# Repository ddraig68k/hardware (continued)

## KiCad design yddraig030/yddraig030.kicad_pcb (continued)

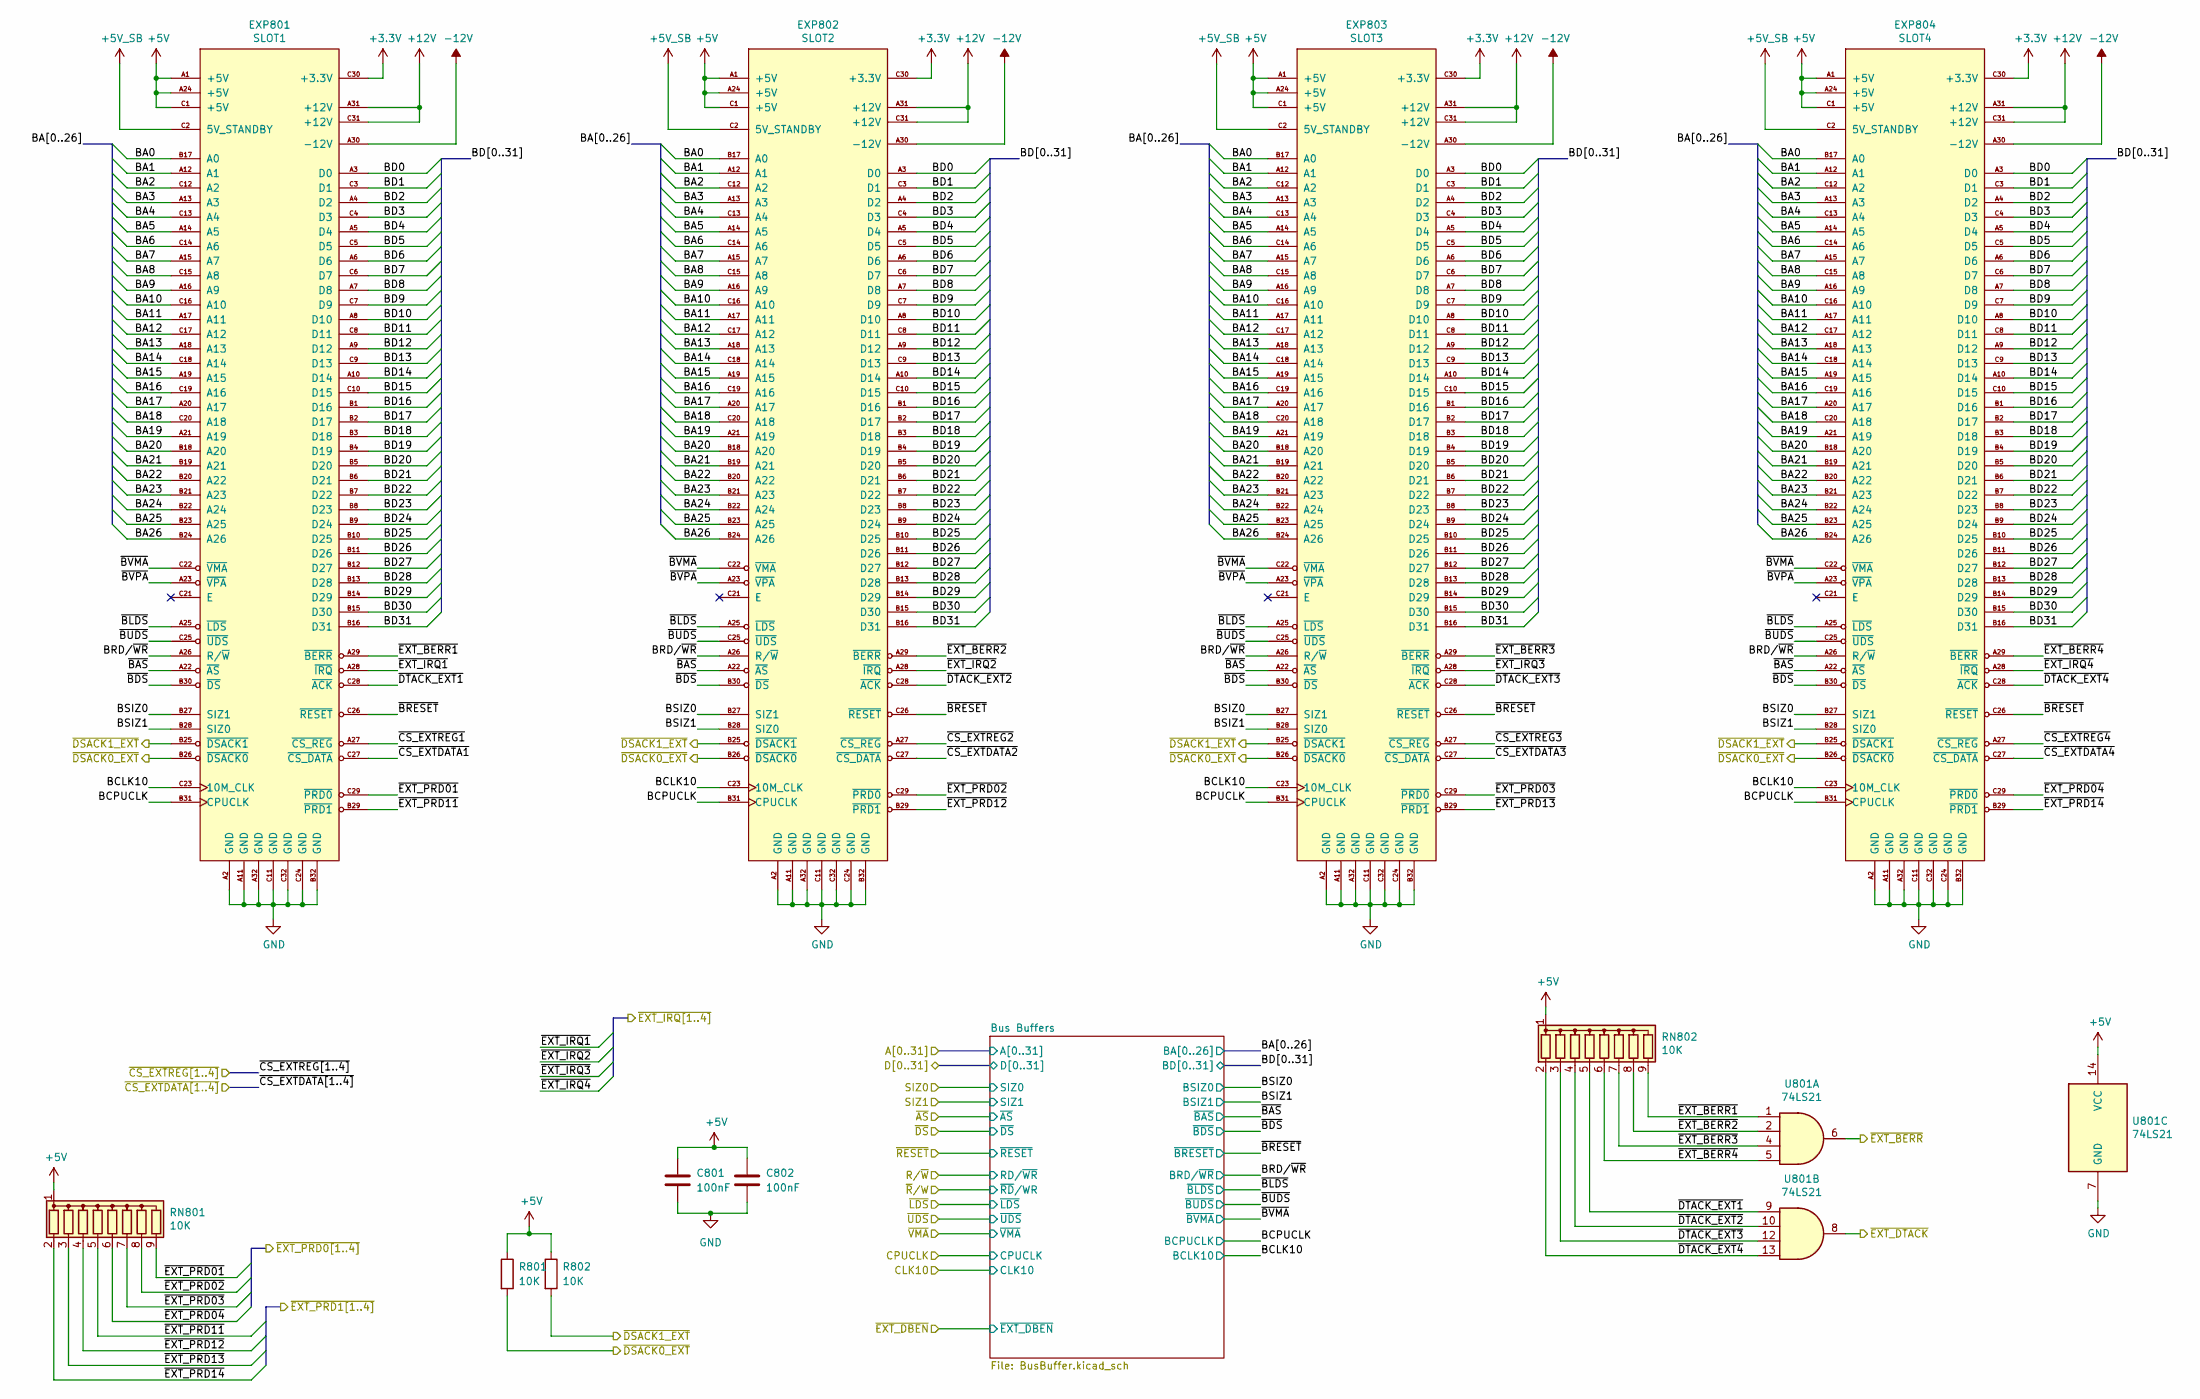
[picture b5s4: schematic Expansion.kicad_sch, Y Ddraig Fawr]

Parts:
C801, C802: 100nF; C_0805_2012Metric
EXP801: SLOT1; DIN41612_C_3x32_Female_Vertical_THT
EXP802: SLOT2; DIN41612_C_3x32_Female_Vertical_THT
EXP803: SLOT3; DIN41612_C_3x32_Female_Vertical_THT
EXP804: SLOT4; DIN41612_C_3x32_Female_Vertical_THT
R801, R802: 10K; R_0805_2012Metric
RN801, RN802: 10K; R_Array_SIP9
U801: 74LS21; SO-14_3.9x8.65mm_P1.27mm

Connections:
+3.3V: EXP801.C30 (+3.3V), EXP802.C30 (+3.3V), EXP803.C30 (+3.3V), EXP804.C30 (+3.3V); also elsewhere on the board
+5V: C801.1, C802.1, EXP801.A1 (+5V), EXP801.A24 (+5V), EXP801.C1 (+5V), EXP802.A1 (+5V), EXP802.A24 (+5V), EXP802.C1 (+5V), EXP803.A1 (+5V), EXP803.A24 (+5V), EXP803.C1 (+5V), EXP804.A1 (+5V), EXP804.A24 (+5V), EXP804.C1 (+5V), R801.1, R802.1, RN801.1 (common), RN802.1 (common), U801.14 (VCC); also elsewhere on the board
+5V_SB: EXP801.C2 (5V_STANDBY), EXP802.C2 (5V_STANDBY), EXP803.C2 (5V_STANDBY), EXP804.C2 (5V_STANDBY); also elsewhere on the board
+12V: EXP801.A31 (+12V), EXP801.C31 (+12V), EXP802.A31 (+12V), EXP802.C31 (+12V), EXP803.A31 (+12V), EXP803.C31 (+12V), EXP804.A31 (+12V), EXP804.C31 (+12V); also elsewhere on the board
-12V: EXP801.A30 (-12V), EXP802.A30 (-12V), EXP803.A30 (-12V), EXP804.A30 (-12V); also elsewhere on the board
/Decode and Logic/~DSACK0_EXT: EXP801.B26 (~DSACK0), EXP802.B26 (~DSACK0), EXP803.B26 (~DSACK0), EXP804.B26 (~DSACK0), R801.2; also elsewhere on the board
/Decode and Logic/~DSACK1_EXT: EXP801.B25 (~DSACK1), EXP802.B25 (~DSACK1), EXP803.B25 (~DSACK1), EXP804.B25 (~DSACK1), R802.2; also elsewhere on the board
/Decode and Logic/~EXT_BERR: U801.6; also elsewhere on the board
/Decode and Logic/~EXT_DTACK: U801.8; also elsewhere on the board
/Decode and Logic/~EXT_PRD01: EXP801.C29 (~PRD0), RN801.9 (R8); also elsewhere on the board
/Decode and Logic/~EXT_PRD02: EXP802.C29 (~PRD0), RN801.8 (R7); also elsewhere on the board
/Decode and Logic/~EXT_PRD03: EXP803.C29 (~PRD0), RN801.7 (R6); also elsewhere on the board
/Decode and Logic/~EXT_PRD04: EXP804.C29 (~PRD0), RN801.6 (R5); also elsewhere on the board
/Decode and Logic/~EXT_PRD11: EXP801.B29 (~PRD1), RN801.5 (R4); also elsewhere on the board
/Decode and Logic/~EXT_PRD12: EXP802.B29 (~PRD1), RN801.4 (R3); also elsewhere on the board
/Decode and Logic/~EXT_PRD13: EXP803.B29 (~PRD1), RN801.3 (R2); also elsewhere on the board
/Decode and Logic/~EXT_PRD14: EXP804.B29 (~PRD1), RN801.2 (R1); also elsewhere on the board
/Expansion Slots/BA0: EXP801.B17 (A0), EXP802.B17 (A0), EXP803.B17 (A0), EXP804.B17 (A0); also elsewhere on the board
/Expansion Slots/BA1: EXP801.A12 (A1), EXP802.A12 (A1), EXP803.A12 (A1), EXP804.A12 (A1); also elsewhere on the board
/Expansion Slots/BA2: EXP801.C12 (A2), EXP802.C12 (A2), EXP803.C12 (A2), EXP804.C12 (A2); also elsewhere on the board
/Expansion Slots/BA3: EXP801.A13 (A3), EXP802.A13 (A3), EXP803.A13 (A3), EXP804.A13 (A3); also elsewhere on the board
/Expansion Slots/BA4: EXP801.C13 (A4), EXP802.C13 (A4), EXP803.C13 (A4), EXP804.C13 (A4); also elsewhere on the board
/Expansion Slots/BA5: EXP801.A14 (A5), EXP802.A14 (A5), EXP803.A14 (A5), EXP804.A14 (A5); also elsewhere on the board
/Expansion Slots/BA6: EXP801.C14 (A6), EXP802.C14 (A6), EXP803.C14 (A6), EXP804.C14 (A6); also elsewhere on the board
/Expansion Slots/BA7: EXP801.A15 (A7), EXP802.A15 (A7), EXP803.A15 (A7), EXP804.A15 (A7); also elsewhere on the board
/Expansion Slots/BA8: EXP801.C15 (A8), EXP802.C15 (A8), EXP803.C15 (A8), EXP804.C15 (A8); also elsewhere on the board
/Expansion Slots/BA9: EXP801.A16 (A9), EXP802.A16 (A9), EXP803.A16 (A9), EXP804.A16 (A9); also elsewhere on the board
/Expansion Slots/BA10: EXP801.C16 (A10), EXP802.C16 (A10), EXP803.C16 (A10), EXP804.C16 (A10); also elsewhere on the board
/Expansion Slots/BA11: EXP801.A17 (A11), EXP802.A17 (A11), EXP803.A17 (A11), EXP804.A17 (A11); also elsewhere on the board
/Expansion Slots/BA12: EXP801.C17 (A12), EXP802.C17 (A12), EXP803.C17 (A12), EXP804.C17 (A12); also elsewhere on the board
/Expansion Slots/BA13: EXP801.A18 (A13), EXP802.A18 (A13), EXP803.A18 (A13), EXP804.A18 (A13); also elsewhere on the board
/Expansion Slots/BA14: EXP801.C18 (A14), EXP802.C18 (A14), EXP803.C18 (A14), EXP804.C18 (A14); also elsewhere on the board
/Expansion Slots/BA15: EXP801.A19 (A15), EXP802.A19 (A15), EXP803.A19 (A15), EXP804.A19 (A15); also elsewhere on the board
/Expansion Slots/BA16: EXP801.C19 (A16), EXP802.C19 (A16), EXP803.C19 (A16), EXP804.C19 (A16); also elsewhere on the board
/Expansion Slots/BA17: EXP801.A20 (A17), EXP802.A20 (A17), EXP803.A20 (A17), EXP804.A20 (A17); also elsewhere on the board
/Expansion Slots/BA18: EXP801.C20 (A18), EXP802.C20 (A18), EXP803.C20 (A18), EXP804.C20 (A18); also elsewhere on the board
/Expansion Slots/BA19: EXP801.A21 (A19), EXP802.A21 (A19), EXP803.A21 (A19), EXP804.A21 (A19); also elsewhere on the board
/Expansion Slots/BA20: EXP801.B18 (A20), EXP802.B18 (A20), EXP803.B18 (A20), EXP804.B18 (A20); also elsewhere on the board
/Expansion Slots/BA21: EXP801.B19 (A21), EXP802.B19 (A21), EXP803.B19 (A21), EXP804.B19 (A21); also elsewhere on the board
/Expansion Slots/BA22: EXP801.B20 (A22), EXP802.B20 (A22), EXP803.B20 (A22), EXP804.B20 (A22); also elsewhere on the board
/Expansion Slots/BA23: EXP801.B21 (A23), EXP802.B21 (A23), EXP803.B21 (A23), EXP804.B21 (A23); also elsewhere on the board
/Expansion Slots/BA24: EXP801.B22 (A24), EXP802.B22 (A24), EXP803.B22 (A24), EXP804.B22 (A24); also elsewhere on the board
/Expansion Slots/BA25: EXP801.B23 (A25), EXP802.B23 (A25), EXP803.B23 (A25), EXP804.B23 (A25); also elsewhere on the board
/Expansion Slots/BA26: EXP801.B24 (A26), EXP802.B24 (A26), EXP803.B24 (A26), EXP804.B24 (A26); also elsewhere on the board
/Expansion Slots/BCLK10: EXP801.C23 (10M_CLK), EXP802.C23 (10M_CLK), EXP803.C23 (10M_CLK), EXP804.C23 (10M_CLK); also elsewhere on the board
/Expansion Slots/BCPUCLK: EXP801.B31 (CPUCLK), EXP802.B31 (CPUCLK), EXP803.B31 (CPUCLK), EXP804.B31 (CPUCLK); also elsewhere on the board
/Expansion Slots/BD0: EXP801.A3 (D0), EXP802.A3 (D0), EXP803.A3 (D0), EXP804.A3 (D0); also elsewhere on the board
/Expansion Slots/BD1: EXP801.C3 (D1), EXP802.C3 (D1), EXP803.C3 (D1), EXP804.C3 (D1); also elsewhere on the board
/Expansion Slots/BD2: EXP801.A4 (D2), EXP802.A4 (D2), EXP803.A4 (D2), EXP804.A4 (D2); also elsewhere on the board
/Expansion Slots/BD3: EXP801.C4 (D3), EXP802.C4 (D3), EXP803.C4 (D3), EXP804.C4 (D3); also elsewhere on the board
/Expansion Slots/BD4: EXP801.A5 (D4), EXP802.A5 (D4), EXP803.A5 (D4), EXP804.A5 (D4); also elsewhere on the board
/Expansion Slots/BD5: EXP801.C5 (D5), EXP802.C5 (D5), EXP803.C5 (D5), EXP804.C5 (D5); also elsewhere on the board
/Expansion Slots/BD6: EXP801.A6 (D6), EXP802.A6 (D6), EXP803.A6 (D6), EXP804.A6 (D6); also elsewhere on the board
/Expansion Slots/BD7: EXP801.C6 (D7), EXP802.C6 (D7), EXP803.C6 (D7), EXP804.C6 (D7); also elsewhere on the board
/Expansion Slots/BD8: EXP801.A7 (D8), EXP802.A7 (D8), EXP803.A7 (D8), EXP804.A7 (D8); also elsewhere on the board
/Expansion Slots/BD9: EXP801.C7 (D9), EXP802.C7 (D9), EXP803.C7 (D9), EXP804.C7 (D9); also elsewhere on the board
/Expansion Slots/BD10: EXP801.A8 (D10), EXP802.A8 (D10), EXP803.A8 (D10), EXP804.A8 (D10); also elsewhere on the board
/Expansion Slots/BD11: EXP801.C8 (D11), EXP802.C8 (D11), EXP803.C8 (D11), EXP804.C8 (D11); also elsewhere on the board
/Expansion Slots/BD12: EXP801.A9 (D12), EXP802.A9 (D12), EXP803.A9 (D12), EXP804.A9 (D12); also elsewhere on the board
/Expansion Slots/BD13: EXP801.C9 (D13), EXP802.C9 (D13), EXP803.C9 (D13), EXP804.C9 (D13); also elsewhere on the board
/Expansion Slots/BD14: EXP801.A10 (D14), EXP802.A10 (D14), EXP803.A10 (D14), EXP804.A10 (D14); also elsewhere on the board
/Expansion Slots/BD15: EXP801.C10 (D15), EXP802.C10 (D15), EXP803.C10 (D15), EXP804.C10 (D15); also elsewhere on the board
/Expansion Slots/BD16: EXP801.B1 (D16), EXP802.B1 (D16), EXP803.B1 (D16), EXP804.B1 (D16); also elsewhere on the board
/Expansion Slots/BD17: EXP801.B2 (D17), EXP802.B2 (D17), EXP803.B2 (D17), EXP804.B2 (D17); also elsewhere on the board
/Expansion Slots/BD18: EXP801.B3 (D18), EXP802.B3 (D18), EXP803.B3 (D18), EXP804.B3 (D18); also elsewhere on the board
/Expansion Slots/BD19: EXP801.B4 (D19), EXP802.B4 (D19), EXP803.B4 (D19), EXP804.B4 (D19); also elsewhere on the board
/Expansion Slots/BD20: EXP801.B5 (D20), EXP802.B5 (D20), EXP803.B5 (D20), EXP804.B5 (D20); also elsewhere on the board
/Expansion Slots/BD21: EXP801.B6 (D21), EXP802.B6 (D21), EXP803.B6 (D21), EXP804.B6 (D21); also elsewhere on the board
/Expansion Slots/BD22: EXP801.B7 (D22), EXP802.B7 (D22), EXP803.B7 (D22), EXP804.B7 (D22); also elsewhere on the board
/Expansion Slots/BD23: EXP801.B8 (D23), EXP802.B8 (D23), EXP803.B8 (D23), EXP804.B8 (D23); also elsewhere on the board
/Expansion Slots/BD24: EXP801.B9 (D24), EXP802.B9 (D24), EXP803.B9 (D24), EXP804.B9 (D24); also elsewhere on the board
/Expansion Slots/BD25: EXP801.B10 (D25), EXP802.B10 (D25), EXP803.B10 (D25), EXP804.B10 (D25); also elsewhere on the board
/Expansion Slots/BD26: EXP801.B11 (D26), EXP802.B11 (D26), EXP803.B11 (D26), EXP804.B11 (D26); also elsewhere on the board
/Expansion Slots/BD27: EXP801.B12 (D27), EXP802.B12 (D27), EXP803.B12 (D27), EXP804.B12 (D27); also elsewhere on the board
/Expansion Slots/BD28: EXP801.B13 (D28), EXP802.B13 (D28), EXP803.B13 (D28), EXP804.B13 (D28); also elsewhere on the board
/Expansion Slots/BD29: EXP801.B14 (D29), EXP802.B14 (D29), EXP803.B14 (D29), EXP804.B14 (D29); also elsewhere on the board
/Expansion Slots/BD30: EXP801.B15 (D30), EXP802.B15 (D30), EXP803.B15 (D30), EXP804.B15 (D30); also elsewhere on the board
/Expansion Slots/BD31: EXP801.B16 (D31), EXP802.B16 (D31), EXP803.B16 (D31), EXP804.B16 (D31); also elsewhere on the board
/Expansion Slots/BRD/~WR: EXP801.A26 (R/~W), EXP802.A26 (R/~W), EXP803.A26 (R/~W), EXP804.A26 (R/~W); also elsewhere on the board
/Expansion Slots/BSIZ0: EXP801.B27 (SIZ1), EXP802.B27 (SIZ1), EXP803.B27 (SIZ1), EXP804.B27 (SIZ1); also elsewhere on the board
/Expansion Slots/BSIZ1: EXP801.B28 (SIZ0), EXP802.B28 (SIZ0), EXP803.B28 (SIZ0), EXP804.B28 (SIZ0); also elsewhere on the board
/Expansion Slots/~BAS: EXP801.A22 (~AS), EXP802.A22 (~AS), EXP803.A22 (~AS), EXP804.A22 (~AS); also elsewhere on the board
/Expansion Slots/~BDS: EXP801.B30 (~DS), EXP802.B30 (~DS), EXP803.B30 (~DS), EXP804.B30 (~DS); also elsewhere on the board
/Expansion Slots/~BLDS: EXP801.A25 (~LDS), EXP802.A25 (~LDS), EXP803.A25 (~LDS), EXP804.A25 (~LDS); also elsewhere on the board
/Expansion Slots/~BRESET: EXP801.C26 (~RESET), EXP802.C26 (~RESET), EXP803.C26 (~RESET), EXP804.C26 (~RESET); also elsewhere on the board
/Expansion Slots/~BUDS: EXP801.C25 (~UDS), EXP802.C25 (~UDS), EXP803.C25 (~UDS), EXP804.C25 (~UDS); also elsewhere on the board
/Expansion Slots/~BVMA: EXP801.C22 (~VMA), EXP802.C22 (~VMA), EXP803.C22 (~VMA), EXP804.C22 (~VMA); also elsewhere on the board
/Expansion Slots/~BVPA: EXP801.A23 (~VPA), EXP802.A23 (~VPA), EXP803.A23 (~VPA), EXP804.A23 (~VPA)
/Expansion Slots/~CS_EXTDATA1: EXP801.C27 (~CS_DATA); also elsewhere on the board
/Expansion Slots/~CS_EXTDATA2: EXP802.C27 (~CS_DATA); also elsewhere on the board
/Expansion Slots/~CS_EXTDATA3: EXP803.C27 (~CS_DATA); also elsewhere on the board
/Expansion Slots/~CS_EXTDATA4: EXP804.C27 (~CS_DATA); also elsewhere on the board
/Expansion Slots/~CS_EXTREG1: EXP801.A27 (~CS_REG); also elsewhere on the board
/Expansion Slots/~CS_EXTREG2: EXP802.A27 (~CS_REG); also elsewhere on the board
/Expansion Slots/~CS_EXTREG3: EXP803.A27 (~CS_REG); also elsewhere on the board
/Expansion Slots/~CS_EXTREG4: EXP804.A27 (~CS_REG); also elsewhere on the board
/Expansion Slots/~DTACK_EXT1: EXP801.C28 (~ACK), RN802.5 (R4), U801.9
/Expansion Slots/~DTACK_EXT2: EXP802.C28 (~ACK), RN802.4 (R3), U801.10
/Expansion Slots/~DTACK_EXT3: EXP803.C28 (~ACK), RN802.3 (R2), U801.12
/Expansion Slots/~DTACK_EXT4: EXP804.C28 (~ACK), RN802.2 (R1), U801.13
/Expansion Slots/~EXT_BERR1: EXP801.A29 (~BERR), RN802.9 (R8), U801.1
/Expansion Slots/~EXT_BERR2: EXP802.A29 (~BERR), RN802.8 (R7), U801.2
/Expansion Slots/~EXT_BERR3: EXP803.A29 (~BERR), RN802.7 (R6), U801.4
/Expansion Slots/~EXT_BERR4: EXP804.A29 (~BERR), RN802.6 (R5), U801.5
/Expansion Slots/~EXT_IRQ1: EXP801.A28 (~IRQ); also elsewhere on the board
/Expansion Slots/~EXT_IRQ2: EXP802.A28 (~IRQ); also elsewhere on the board
/Expansion Slots/~EXT_IRQ3: EXP803.A28 (~IRQ); also elsewhere on the board
/Expansion Slots/~EXT_IRQ4: EXP804.A28 (~IRQ); also elsewhere on the board

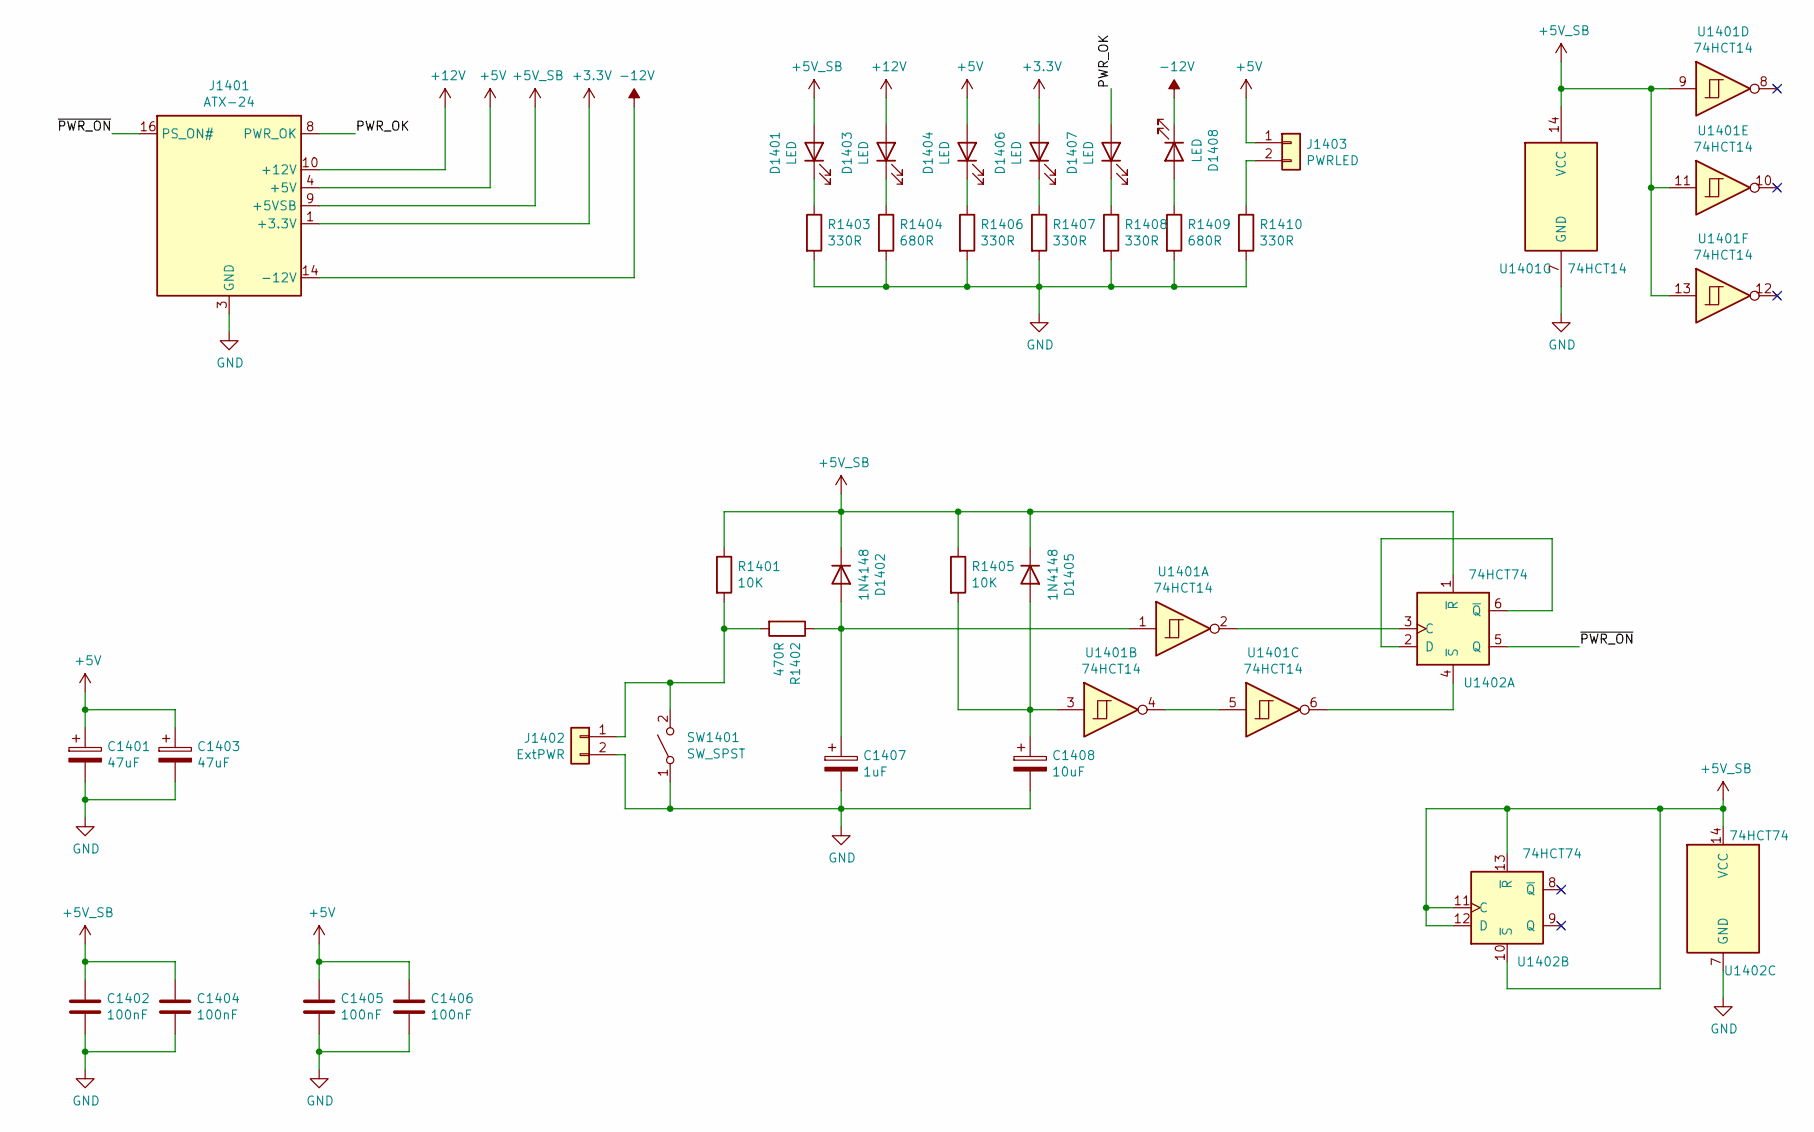
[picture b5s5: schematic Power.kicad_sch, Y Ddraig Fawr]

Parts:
C1401, C1403: 47uF; CP_Elec_4x5.3
C1402, C1404, C1405, C1406: 100nF; C_0805_2012Metric
C1407: 1uF; CP_Elec_4x5.3
C1408: 10uF; CP_Elec_4x5.3
D1401, D1403, D1404, D1406, D1407, D1408: LED; LED_1206_3216Metric
D1402, D1405: 1N4148; D_SOD-123
J1401: ATX-24; 1-1775099-3
J1402: ExtPWR; PinHeader_1x02_P2.54mm_Vertical
J1403: PWRLED; PinHeader_1x02_P2.54mm_Vertical
R1401, R1405: 10K; R_0805_2012Metric
R1402: 470R; R_0805_2012Metric
R1403, R1406, R1407, R1408, R1410: 330R; R_0805_2012Metric
R1404, R1409: 680R; R_0805_2012Metric
SW1401: SW_SPST; SW_PUSH_6mm_H4.3mm
U1401: 74HCT14; SO-14_3.9x8.65mm_P1.27mm
U1402: 74HCT74; SO-14_3.9x8.65mm_P1.27mm

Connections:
+3.3V: D1406.2 (A), J1401.1 (+3.3V), J1401.2 (+3.3V), J1401.12 (+3.3V), J1401.13 (+3.3V); also elsewhere on the board
+5V: C1401.1, C1403.1, C1405.1, C1406.1, D1404.2 (A), J1401.4 (+5V), J1401.6 (+5V), J1401.21 (+5V), J1401.22 (+5V), J1401.23 (+5V), J1403.1; also elsewhere on the board
+5V_SB: C1402.1, C1404.1, D1401.2 (A), D1402.1 (K), D1405.1 (K), J1401.9 (+5VSB), R1401.1, R1405.1, U1401.9, U1401.11, U1401.13, U1401.14 (VCC), U1402.1 (~R), U1402.10 (~S), U1402.11 (C), U1402.12 (D), U1402.13 (~R), U1402.14 (VCC); also elsewhere on the board
+12V: D1403.2 (A), J1401.10 (+12V), J1401.11 (+12V); also elsewhere on the board
-12V: D1408.1 (K), J1401.14 (-12V); also elsewhere on the board
/Power/PWR_OK: D1407.2 (A), J1401.8 (PWR_OK)
/Power/~PWR_ON: J1401.16 (PS_ON#), U1402.5 (Q)
unnamed: C1407.1, D1402.2 (A), R1402.1, U1401.1
unnamed: C1408.1, D1405.2 (A), R1405.2, U1401.3
unnamed: D1401.1 (K), R1403.1
unnamed: D1403.1 (K), R1404.1
unnamed: D1404.1 (K), R1406.1
unnamed: D1406.1 (K), R1407.1
unnamed: D1407.1 (K), R1408.1
unnamed: D1408.2 (A), R1409.1
unnamed: J1402.1, R1401.2, R1402.2, SW1401.2 (B)
unnamed: J1403.2, R1410.1
unnamed: U1401.2, U1402.3 (C)
unnamed: U1401.4, U1401.5
unnamed: U1401.6, U1402.4 (~S)
unnamed: U1402.2 (D), U1402.6 (~Q)

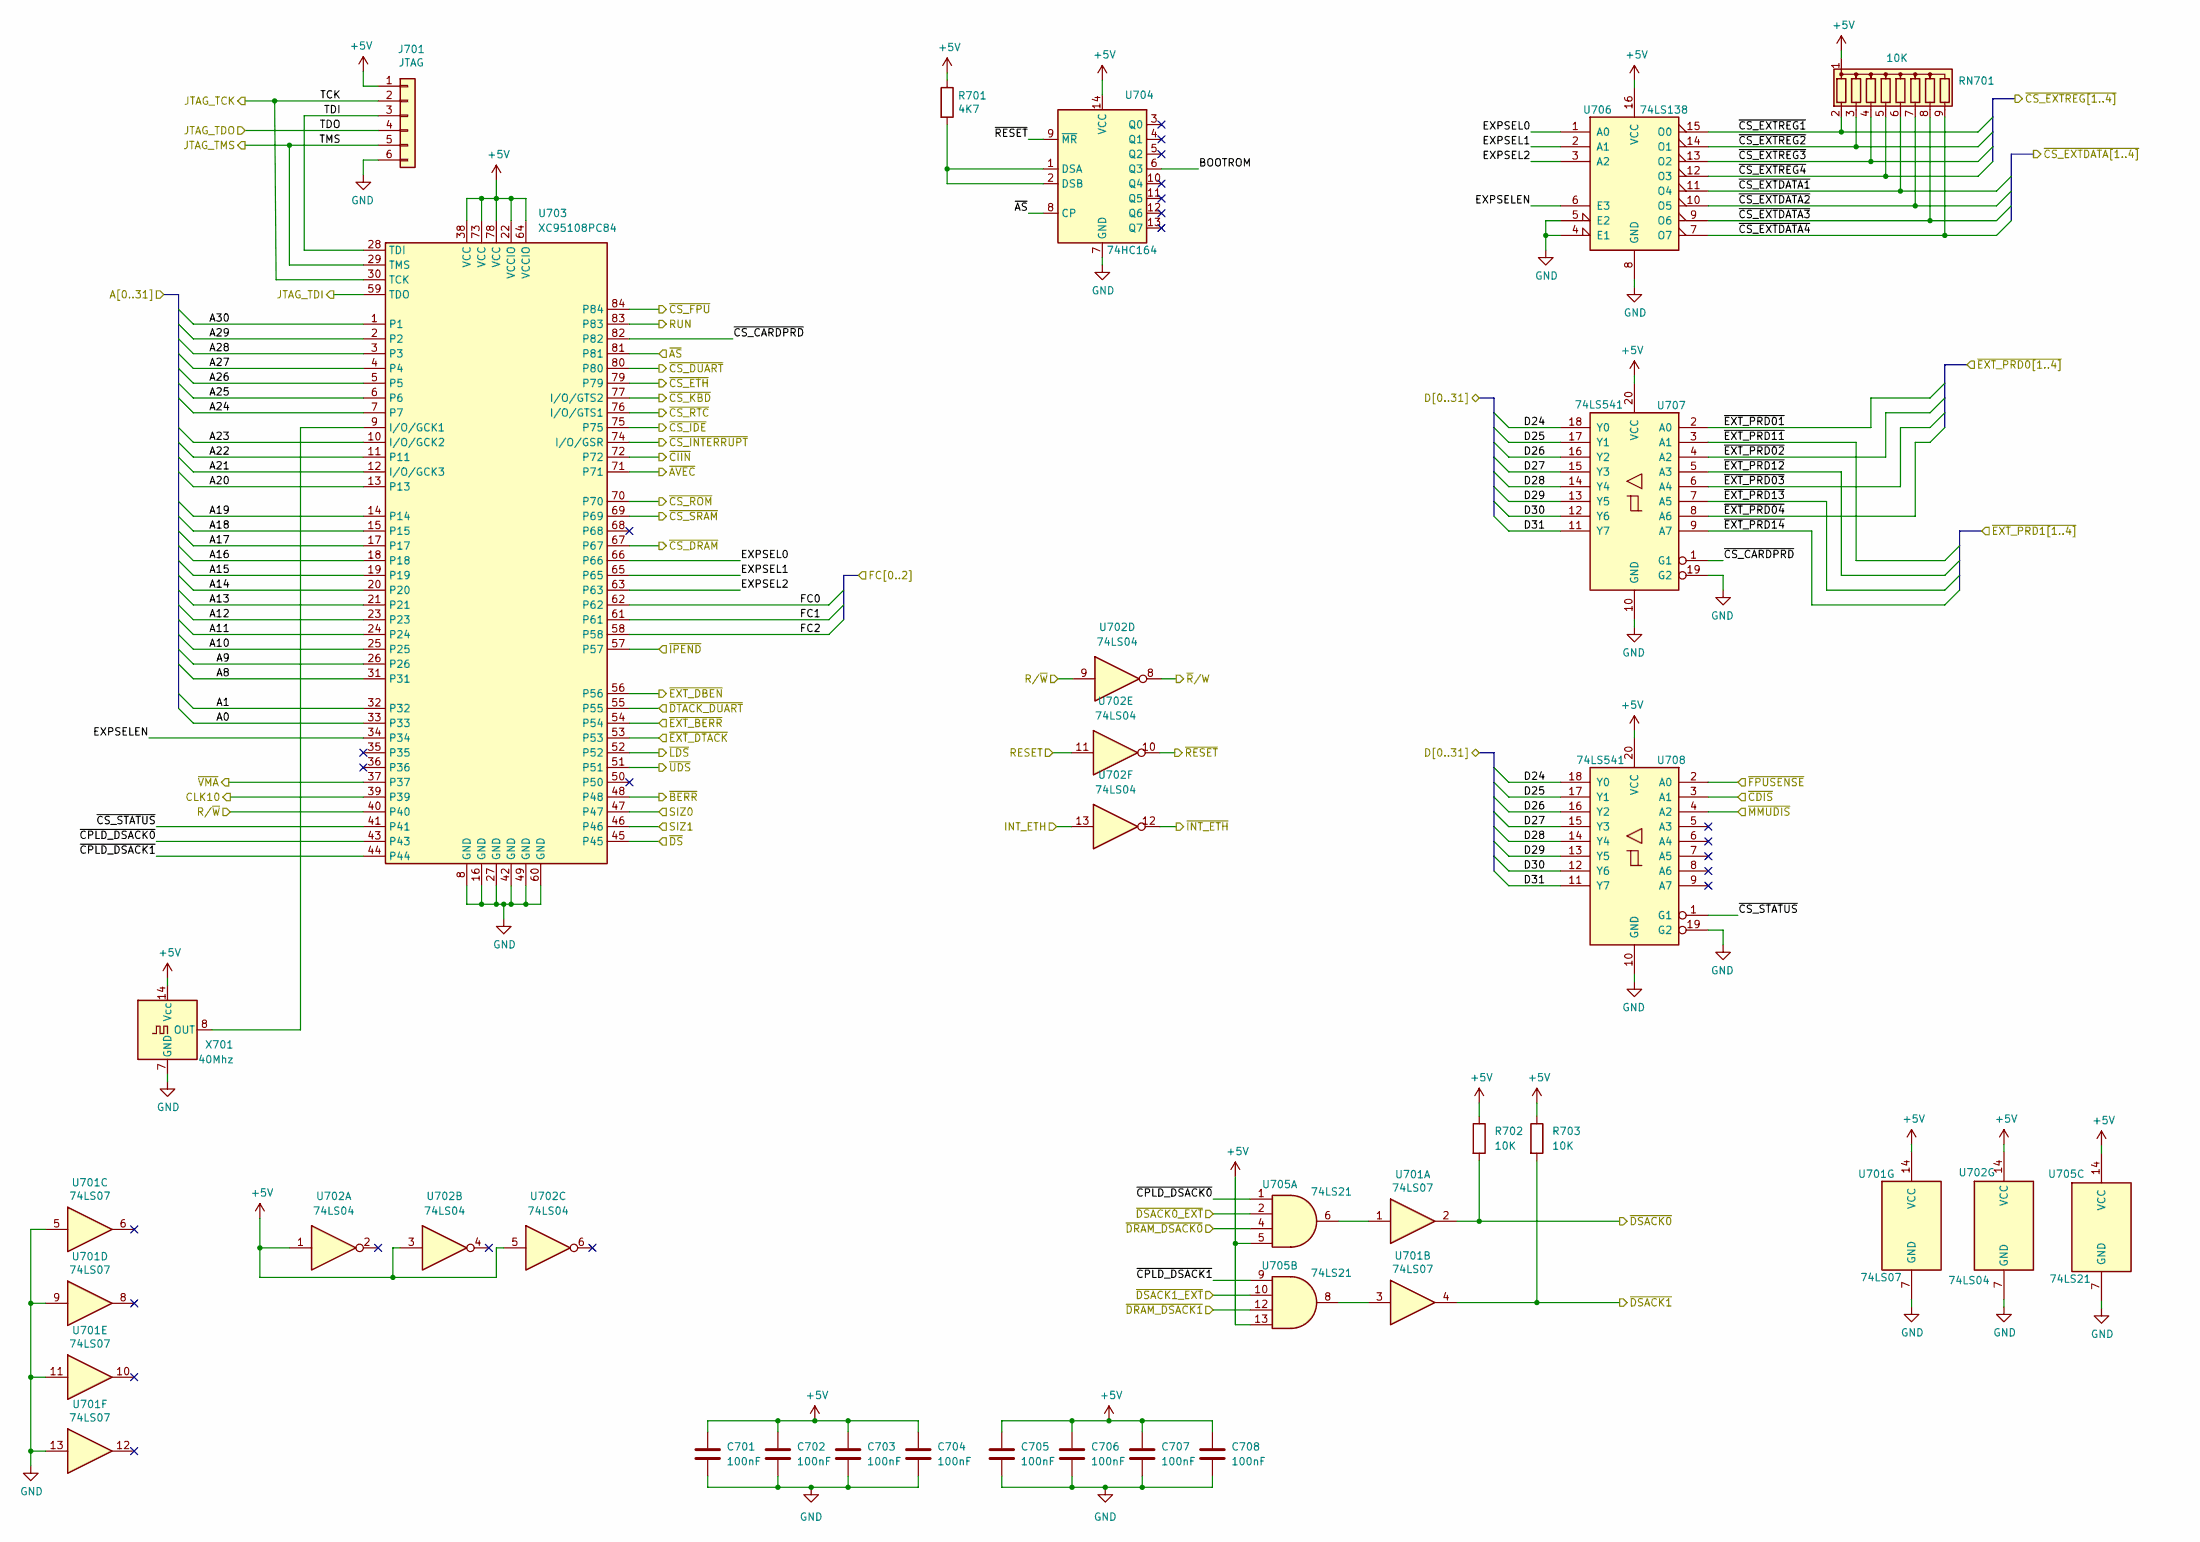
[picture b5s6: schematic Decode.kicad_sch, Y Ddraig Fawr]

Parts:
C701, C702, C703, C704, C705, C706, C707, C708: 100nF; C_0805_2012Metric
J701: JTAG; PinSocket_1x06_P2.54mm_Vertical
R701: 4K7; R_0805_2012Metric
R702, R703: 10K; R_0805_2012Metric
RN701: 10K; R_Array_SIP9
U701: 74LS07; SO-14_3.9x8.65mm_P1.27mm
U702: 74LS04; SO-14_3.9x8.65mm_P1.27mm
U703: XC95108PC84; PLCC-84_THT-Socket
U704: 74HC164; SO-14_3.9x8.65mm_P1.27mm
U705: 74LS21; SO-14_3.9x8.65mm_P1.27mm
U706: 74LS138; SO-16_3.9x9.9mm_P1.27mm
U707, U708: 74LS541; SO-20_5.3x12.6mm_P1.27mm
X701: 40Mhz; Oscillator_DIP-14

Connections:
+5V: C701.1, C702.1, C703.1, C704.1, C705.1, C706.1, C707.1, C708.1, J701.1, R701.1, R702.1, R703.1, RN701.1 (common), U701.14 (VCC), U702.1, U702.3, U702.5, U702.14 (VCC), U703.22 (VCCIO), U703.38 (VCC), U703.64 (VCCIO), U703.73 (VCC), U703.78 (VCC), U704.14 (VCC), U705.5, U705.13, U705.14 (VCC), U706.16 (VCC), U707.20 (VCC), U708.20 (VCC), X701.14 (Vcc); also elsewhere on the board
/CPU and FPU/FC0: U703.62; also elsewhere on the board
/CPU and FPU/FC1: U703.61; also elsewhere on the board
/CPU and FPU/FC2: U703.58; also elsewhere on the board
/CPU and FPU/R/~W: U702.9, U703.40; also elsewhere on the board
/CPU and FPU/~AS: U703.81, U704.8 (CP); also elsewhere on the board
/CPU and FPU/~AVEC: U703.71; also elsewhere on the board
/CPU and FPU/~BERR: U703.48; also elsewhere on the board
/CPU and FPU/~CDIS: U708.3 (A1); also elsewhere on the board
/CPU and FPU/~CIIN: U703.72; also elsewhere on the board
/CPU and FPU/~CS_FPU: U703.84; also elsewhere on the board
/CPU and FPU/~DSACK0: R702.2, U701.2; also elsewhere on the board
/CPU and FPU/~DSACK1: R703.2, U701.4; also elsewhere on the board
/CPU and FPU/~DS: U703.45; also elsewhere on the board
/CPU and FPU/~FPUSENSE: U708.2 (A0); also elsewhere on the board
/CPU and FPU/~IPEND: U703.57; also elsewhere on the board
/CPU and FPU/~MMUDIS: U708.4 (A2); also elsewhere on the board
/CPU and FPU/~RESET: U702.10, U704.9 (~MR); also elsewhere on the board
/DRAM/JTAG_TDI: U703.59 (TDO); also elsewhere on the board
/DRAM/~CS_DRAM: U703.67; also elsewhere on the board
/DRAM/~DSACK0: U705.4; also elsewhere on the board
/DRAM/~DSACK1: U705.12; also elsewhere on the board
/Decode and Logic/BOOTROM: U704.6 (Q3)
/Decode and Logic/CLK10: U703.39; also elsewhere on the board
/Decode and Logic/EXPSEL0: U703.66, U706.1 (A0)
/Decode and Logic/EXPSEL1: U703.65, U706.2 (A1)
/Decode and Logic/EXPSEL2: U703.63, U706.3 (A2)
/Decode and Logic/EXPSELEN: U703.34, U706.6 (E3)
/Decode and Logic/INT_ETH: U702.13; also elsewhere on the board
/Decode and Logic/RESET: U702.11; also elsewhere on the board
/Decode and Logic/RUN: U703.83; also elsewhere on the board
/Decode and Logic/SIZ0: U703.47
/Decode and Logic/SIZ1: U703.46
/Decode and Logic/TCK: J701.2, U703.30 (TCK); also elsewhere on the board
/Decode and Logic/TDI: J701.3, U703.28 (TDI)
/Decode and Logic/TDO: J701.4; also elsewhere on the board
/Decode and Logic/TMS: J701.5, U703.29 (TMS); also elsewhere on the board
/Decode and Logic/~CPLD_DSACK0: U703.43, U705.1
/Decode and Logic/~CPLD_DSACK1: U703.44, U705.9
/Decode and Logic/~CS_CARDPRD: U703.82, U707.1 (G1)
/Decode and Logic/~CS_DUART: U703.80; also elsewhere on the board
/Decode and Logic/~CS_ETH: U703.79; also elsewhere on the board
/Decode and Logic/~CS_IDE: U703.75; also elsewhere on the board
/Decode and Logic/~CS_INTERRUPT: U703.74 (I/O/GSR); also elsewhere on the board
/Decode and Logic/~CS_KBD: U703.77 (I/O/GTS2); also elsewhere on the board
/Decode and Logic/~CS_ROM: U703.70; also elsewhere on the board
/Decode and Logic/~CS_RTC: U703.76 (I/O/GTS1); also elsewhere on the board
/Decode and Logic/~CS_SRAM: U703.69; also elsewhere on the board
/Decode and Logic/~CS_STATUS: U703.41, U708.1 (G1)
/Decode and Logic/~DSACK0_EXT: U705.2; also elsewhere on the board
/Decode and Logic/~DSACK1_EXT: U705.10; also elsewhere on the board
/Decode and Logic/~DTACK_DUART: U703.55; also elsewhere on the board
/Decode and Logic/~EXT_BERR: U703.54; also elsewhere on the board
/Decode and Logic/~EXT_DBEN: U703.56; also elsewhere on the board
/Decode and Logic/~EXT_DTACK: U703.53; also elsewhere on the board
/Decode and Logic/~EXT_PRD01: U707.2 (A0); also elsewhere on the board
/Decode and Logic/~EXT_PRD02: U707.4 (A2); also elsewhere on the board
/Decode and Logic/~EXT_PRD03: U707.6 (A4); also elsewhere on the board
/Decode and Logic/~EXT_PRD04: U707.8 (A6); also elsewhere on the board
/Decode and Logic/~EXT_PRD11: U707.3 (A1); also elsewhere on the board
/Decode and Logic/~EXT_PRD12: U707.5 (A3); also elsewhere on the board
/Decode and Logic/~EXT_PRD13: U707.7 (A5); also elsewhere on the board
/Decode and Logic/~EXT_PRD14: U707.9 (A7); also elsewhere on the board
/Decode and Logic/~INT_ETH: U702.12; also elsewhere on the board
/Decode and Logic/~LDS: U703.52; also elsewhere on the board
/Decode and Logic/~R/W: U702.8; also elsewhere on the board
/Decode and Logic/~UDS: U703.51; also elsewhere on the board
/Decode and Logic/~VMA: U703.37; also elsewhere on the board
/Expansion Slots/~CS_EXTDATA1: RN701.6 (R5), U706.11 (O4); also elsewhere on the board
/Expansion Slots/~CS_EXTDATA2: RN701.7 (R6), U706.10 (O5); also elsewhere on the board
/Expansion Slots/~CS_EXTDATA3: RN701.8 (R7), U706.9 (O6); also elsewhere on the board
/Expansion Slots/~CS_EXTDATA4: RN701.9 (R8), U706.7 (O7); also elsewhere on the board
/Expansion Slots/~CS_EXTREG1: RN701.2 (R1), U706.15 (O0); also elsewhere on the board
/Expansion Slots/~CS_EXTREG2: RN701.3 (R2), U706.14 (O1); also elsewhere on the board
/Expansion Slots/~CS_EXTREG3: RN701.4 (R3), U706.13 (O2); also elsewhere on the board
/Expansion Slots/~CS_EXTREG4: RN701.5 (R4), U706.12 (O3); also elsewhere on the board
/ROM and SRAM/A0: U703.33; also elsewhere on the board
/ROM and SRAM/A1: U703.32; also elsewhere on the board
/ROM and SRAM/A8: U703.31; also elsewhere on the board
/ROM and SRAM/A9: U703.26; also elsewhere on the board
/ROM and SRAM/A10: U703.25; also elsewhere on the board
/ROM and SRAM/A11: U703.24; also elsewhere on the board
/ROM and SRAM/A12: U703.23; also elsewhere on the board
/ROM and SRAM/A13: U703.21; also elsewhere on the board
/ROM and SRAM/A14: U703.20; also elsewhere on the board
/ROM and SRAM/A15: U703.19; also elsewhere on the board
/ROM and SRAM/A16: U703.18; also elsewhere on the board
/ROM and SRAM/A17: U703.17; also elsewhere on the board
/ROM and SRAM/A18: U703.15; also elsewhere on the board
/ROM and SRAM/A19: U703.14; also elsewhere on the board
/ROM and SRAM/A20: U703.13; also elsewhere on the board
/ROM and SRAM/A21: U703.12 (I/O/GCK3); also elsewhere on the board
/ROM and SRAM/A22: U703.11; also elsewhere on the board
/ROM and SRAM/A23: U703.10 (I/O/GCK2); also elsewhere on the board
/ROM and SRAM/A24: U703.7; also elsewhere on the board
/ROM and SRAM/A25: U703.6; also elsewhere on the board
/ROM and SRAM/A26: U703.5; also elsewhere on the board
/ROM and SRAM/A27: U703.4; also elsewhere on the board
/ROM and SRAM/A28: U703.3; also elsewhere on the board
/ROM and SRAM/A29: U703.2; also elsewhere on the board
/ROM and SRAM/A30: U703.1; also elsewhere on the board
/ROM and SRAM/D24: U707.18 (Y0), U708.18 (Y0); also elsewhere on the board
/ROM and SRAM/D25: U707.17 (Y1), U708.17 (Y1); also elsewhere on the board
/ROM and SRAM/D26: U707.16 (Y2), U708.16 (Y2); also elsewhere on the board
/ROM and SRAM/D27: U707.15 (Y3), U708.15 (Y3); also elsewhere on the board
/ROM and SRAM/D28: U707.14 (Y4), U708.14 (Y4); also elsewhere on the board
/ROM and SRAM/D29: U707.13 (Y5), U708.13 (Y5); also elsewhere on the board
/ROM and SRAM/D30: U707.12 (Y6), U708.12 (Y6); also elsewhere on the board
/ROM and SRAM/D31: U707.11 (Y7), U708.11 (Y7); also elsewhere on the board
unnamed: R701.2, U704.1 (DSA), U704.2 (DSB)
unnamed: U701.1, U705.6
unnamed: U701.3, U705.8
unnamed: U703.9 (I/O/GCK1), X701.8 (OUT)
